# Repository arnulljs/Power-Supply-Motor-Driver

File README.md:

# Power Supply + Motor Driver – CpE 2303L Practical Activity

This repository contains the PCB project files for a **Power Supply and Motor Driver Module**, submitted as part of a practical activity in **CpE 2303L: Computer Engineering Drafting and Design**. The design integrates mechanical, electrical, and environmental considerations to ensure safe and reliable performance.

---

## 🧩 Features

- Combined **Power Supply** and **Motor Driver** on a single board
- **Heatsink integration** for TO-220 components
- **Current-rated track widths** based on component datasheets
- **Copper fill zones** for effective GND distribution
- Organized component layout for thermal and mechanical stability

---

## 📐 Design Considerations

### Mechanical
- 4x mounting holes (3.2mm) for stable board installation
- Copper pours help with EMI reduction and heat spreading

### Electrical
- Track widths adjusted based on current ratings from datasheets
- DIP-16 sockets for motor driver ICs (e.g., L293D)
- Barrel jack for DC input

### Environmental
- Heatsink for thermal dissipation on TO-220 components

---

## 🧱 Components Used

| Component | Quantity | Description |
|----------|----------|-------------|
| `Capacitor_THT:CP_Axial_L10.0mm_D4.5mm_P15.00mm_Horizontal` | 3 | Electrolytic capacitors |
| `LED_THT:LED_D1.8mm_W1.8mm_H2.4mm_Horizontal_O1.27mm_Z1.6mm` | 1 | Status/power LED |
| `MountingHole:MountingHole_3.2mm_M3` | 4 | Mounting holes |
| `Connector_PinSocket_2.54mm:PinSocket_1x03_P2.54mm_Vertical` | 3 | Pin headers |
| `Connector_PinSocket_2.54mm:PinSocket_1x02_P2.54mm_Vertical` | 6 | Pin headers |
| `Connector_BarrelJack:BarrelJack_Horizontal` | 1 | DC power input |
| `Resistor_THT:R_Axial_DIN0204_L3.6mm_D1.6mm_P1.90mm_Vertical` | 1 | Resistor (e.g., for LED) |
| `Package_DIP:DIP-16_W7.62mm` | 2 | IC sockets (motor drivers) |
| `Package_TO_SOT_THT:TO-220-3_Vertical` | 2 | TO-220 voltage regulators/drivers |
| `MyLibrary:HEATSINKUS-V` | 1 | Custom TO-220 heatsink footprint |

---

## 🛠️ Custom Heatsink

- **`HEATSINKUS-V`** is a custom symbol and footprint.
- The 3D model was designed in **SketchUp** by **Noxctis**.
- It is stored in the custom library included in this project.

---

## 🙏 Acknowledgment

Credits to **Noxctis** for the custom 3D model of the TO-220 heatsink.

## 📷 Documentation

### Image 1

### Image 2

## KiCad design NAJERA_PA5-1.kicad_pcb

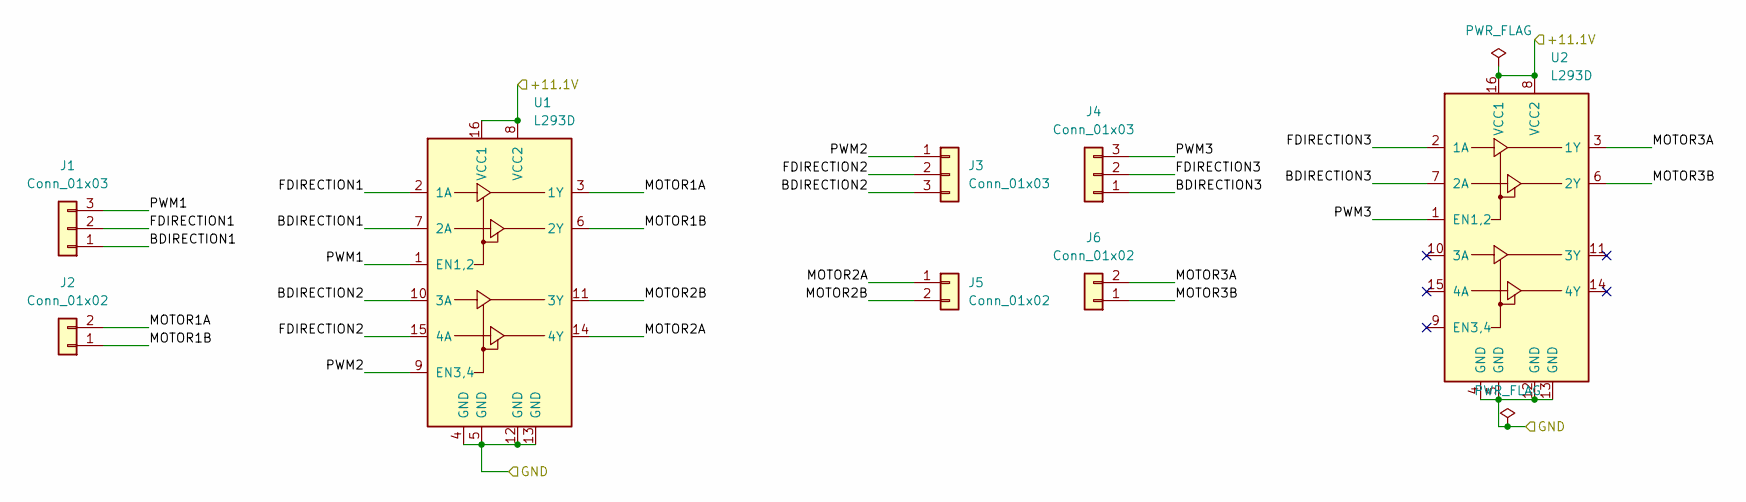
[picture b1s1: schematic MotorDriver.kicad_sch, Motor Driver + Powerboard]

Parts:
J1, J3, J4: Conn_01x03; PinSocket_1x03_P2.54mm_Vertical
J2, J5, J6: Conn_01x02; PinSocket_1x02_P2.54mm_Vertical
U1, U2: L293D; DIP-16_W7.62mm

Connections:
/MotorDriver/+11.1V: U1.8 (VCC2), U1.16 (VCC1), U2.8 (VCC2), U2.16 (VCC1); also elsewhere on the board
/MotorDriver/BDIRECTION1: J1.1, U1.7 (2A)
/MotorDriver/BDIRECTION2: J3.3, U1.10 (3A)
/MotorDriver/BDIRECTION3: J4.1, U2.7 (2A)
/MotorDriver/FDIRECTION1: J1.2, U1.2 (1A)
/MotorDriver/FDIRECTION2: J3.2, U1.15 (4A)
/MotorDriver/FDIRECTION3: J4.2, U2.2 (1A)
/MotorDriver/MOTOR1A: J2.2, U1.3 (1Y)
/MotorDriver/MOTOR1B: J2.1, U1.6 (2Y)
/MotorDriver/MOTOR2A: J5.1, U1.14 (4Y)
/MotorDriver/MOTOR2B: J5.2, U1.11 (3Y)
/MotorDriver/MOTOR3A: J6.2, U2.3 (1Y)
/MotorDriver/MOTOR3B: J6.1, U2.6 (2Y)
/MotorDriver/PWM1: J1.3, U1.1 (EN1,2)
/MotorDriver/PWM2: J3.1, U1.9 (EN3,4)
/MotorDriver/PWM3: J4.3, U2.1 (EN1,2)
GND: U1.4 (GND), U1.5 (GND), U1.12 (GND), U1.13 (GND), U2.4 (GND), U2.5 (GND), U2.12 (GND), U2.13 (GND); also elsewhere on the board

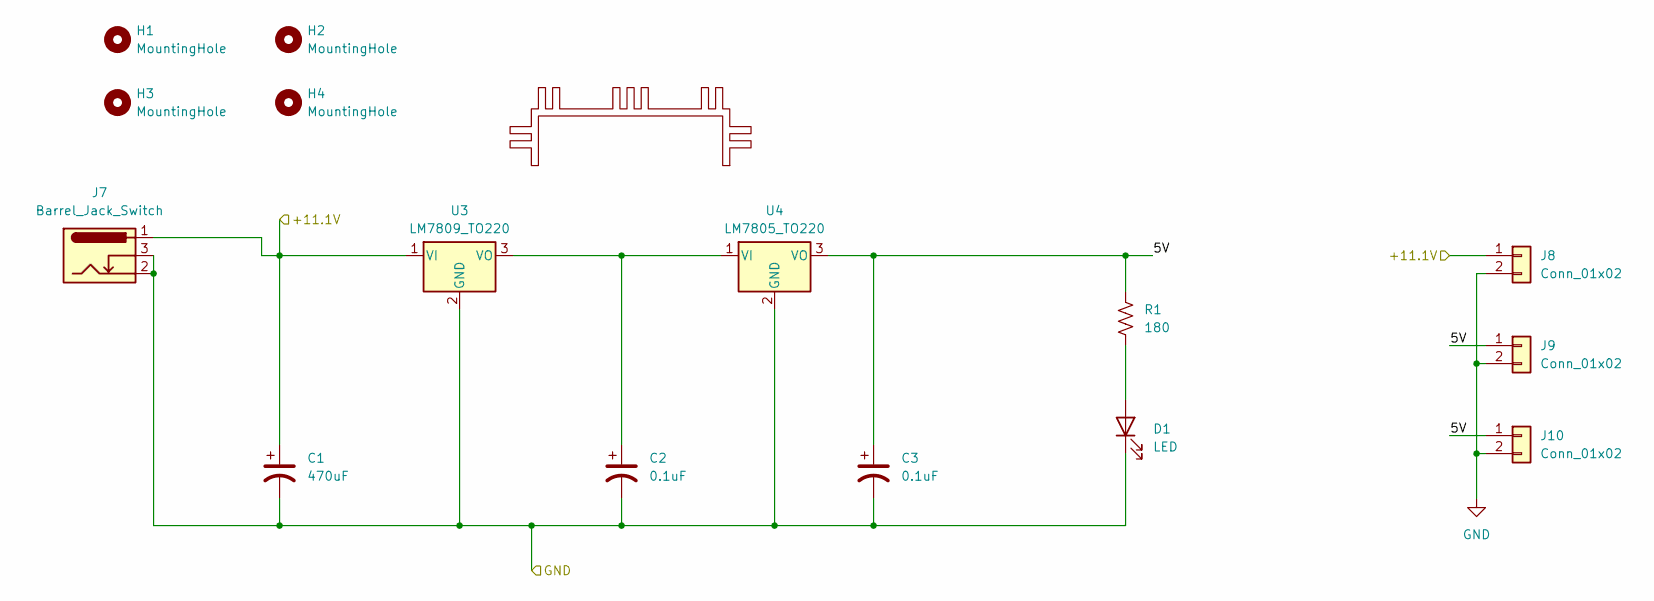
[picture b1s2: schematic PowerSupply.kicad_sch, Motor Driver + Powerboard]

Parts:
C1: 470uF; CP_Axial_L10.0mm_D4.5mm_P15.00mm_Horizontal
C2, C3: 0.1uF; CP_Axial_L10.0mm_D4.5mm_P15.00mm_Horizontal
D1: LED; LED_D1.8mm_W1.8mm_H2.4mm_Horizontal_O1.27mm_Z1.6mm
H1, H2, H3, H4: MountingHole; MountingHole_3.2mm_M3
J7: Barrel_Jack_Switch; BarrelJack_Horizontal
J8, J9, J10: Conn_01x02; PinSocket_1x02_P2.54mm_Vertical
R1: 180; R_Axial_DIN0204_L3.6mm_D1.6mm_P1.90mm_Vertical
U3: LM7809_TO220; TO-220-3_Vertical
U4: LM7805_TO220; TO-220-3_Vertical
U5: HEATSINKUS-V

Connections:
/MotorDriver/+11.1V: C1.1, J7.1, J8.1, U3.1 (VI); also elsewhere on the board
/PowerSupply/5V: C3.1, J9.1, J10.1, R1.1, U4.3 (VO)
GND: C1.2, C2.2, C3.2, D1.1 (K), J7.2, J7.3, J8.2, J9.2, J10.2, U3.2 (GND), U4.2 (GND); also elsewhere on the board
unnamed: D1.2 (A), R1.2
unnamed: C2.1, U3.3 (VO), U4.1 (VI)

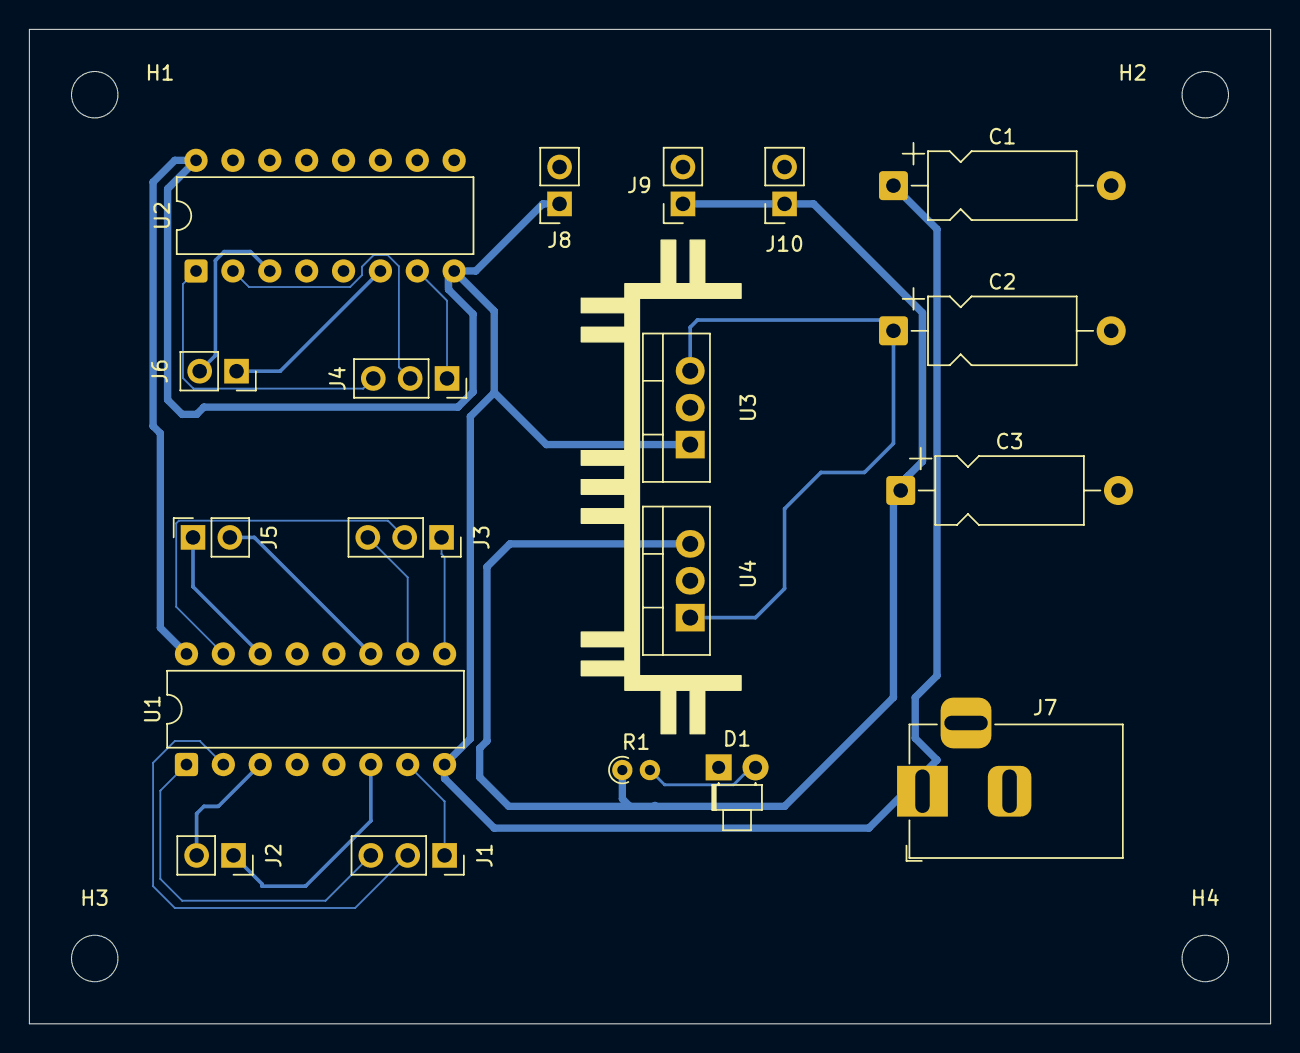
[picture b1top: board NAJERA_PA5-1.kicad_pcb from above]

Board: 2 copper layers, 85.5 x 68.5 mm, 24 parts (0 on the bottom side), 20 nets.

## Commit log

2025-07-29 Added files
2025-07-29 Added documentation images
